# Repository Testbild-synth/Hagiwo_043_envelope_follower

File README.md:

# Hagiwo Eurorack Envelope Follower

This project is a through hole PCB version the HAGIWO 043 envelope follower. I also added a guitar jack input with more amplification to be able to plug in a variety of instruments.

## STATUS: CONFIRMED WORKING! Currently on version 2, if you ordered an older version make sure that the ground connector is correctly connected to all other pcb grounds and also check that the Guitar input is going into the C3 capacitor correctly.

## Hardware and PCB
For this one I wanted to fit it all onto one PCB and make the guitar jack fit. This was quite a task and I'm afraid the pcb ended up a bit messy in the end because of this. It still works fine, but has a lot of overlapping components and you have to be careful when building it.

You can find the schematic and BOM in the root folder. 
For the PCBs, the module has one circuit PCB and one panel PCB. 
You can order them on any common PCB manufacturing service, I used JLCPCB. For the circuit PCB, standard settings should be fine.
For the panel, since it has copper exposed, make sure to choose a lead free surface finish (LeadFree HASL, ENIG) and/or spraypaint your panels so that you don't get lead on your hands.

For assembly, the guitar jack is optional. It will stick out and has to be connected to the rest of the pcb via wires. Look for the pads named "guitar in" and "gnd" on the pcb and connect those to the inner and outer log of a mono guitar/6.5mm jack socket.
Be sure to get a pcb mount guitar jack! we will not be mounting it to the pcb but the ["normal" round ones](https://www.conrad.de/de/p/bkl-electronic-1109001-klinken-steckverbinder-6-35-mm-buchse-einbau-vertikal-polzahl-num-2-mono-silber-1-st-732931.html) don't fit the spacing. I got [this!](https://www.reichelt.de/klinkeneinbaubuchse-6-3-mm-mono-2-pol-ebmsv-63-p36198.html?PROVID=2788&gclid=CjwKCAiAsNKQBhAPEiwAB-I5zdQuMwRXD1BioeI2tvVrd7EJKaeRaZpVK8cO38NI3ps_gF-faOb4TRoCZE0QAvD_BwE)

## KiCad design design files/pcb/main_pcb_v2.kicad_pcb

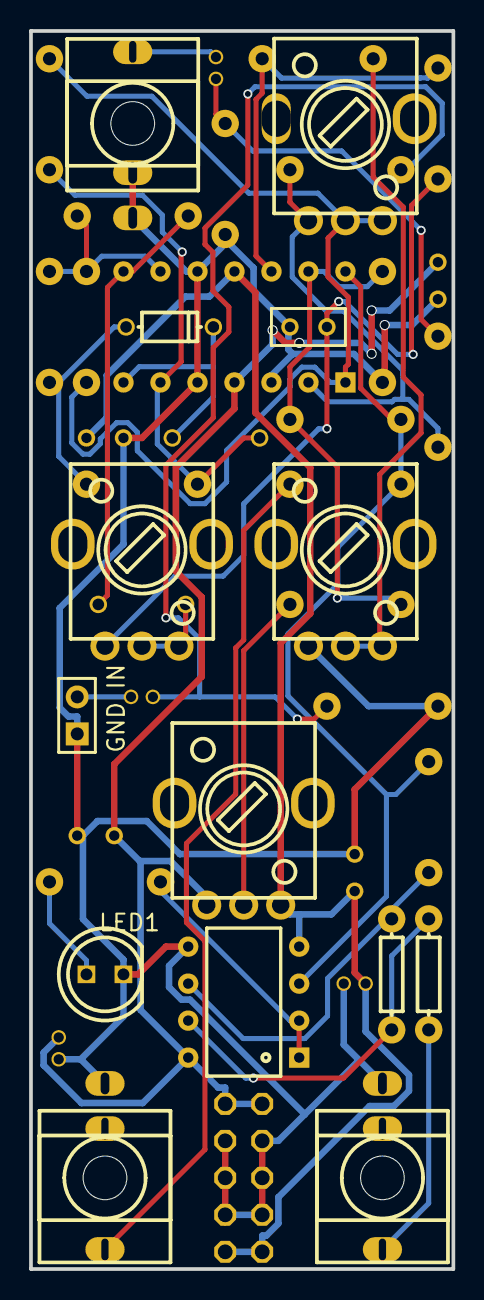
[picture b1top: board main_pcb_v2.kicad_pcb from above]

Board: 2 copper layers, 29.0 x 85.0 mm, 43 parts (0 on the bottom side), 27 nets.

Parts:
ATK: 50k; R09-5KΩ
C1, C3: 4.7u; CAP-D4.0×F1.5
C2: 1u; RAD-0.1
C4, C6, C8, C9: 100n; RAD-0.1
C5, C7: 10u; CAP-D4.0×F1.5
D1, D2, D3: DIODE1N4148; SEEED-DO-35
EP1: EURORACK_POWERHEADER_V2; EURORACK_POWER_V2
GAIN: 100k; R09-5KΩ
H1: GUITAR; HDR-F-2.54_1X2
J1: IN; THONKICONN_1
J2: OUT; THONKICONN_1
J3: INVOUT; THONKICONN_1
LED1: LED_LED5MM
OFFSET: 100k; R09-5KΩ
R1: 20k; R_AXIAL-0.3
R2: 22k; R_AXIAL-0.3
R3, R7, R8, R9, R13, R14, R15, R16, R17: 10k; R_AXIAL-0.3
R4: 47k; R_AXIAL-0.3
R5, R12, R18: 1k; R_AXIAL-0.3
R6, R11: 1M; R_AXIAL-0.3
R10, R19: 4.7k; R_AXIAL-0.3
REL: 1M; R09-5KΩ
U1: TL074CJ; DIP14
U2: TL072IPE4; DIP8

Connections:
12V: C6.2, C7.1, C8.2, EP1.12, OFFSET.1, U1.4, U2.8
-12V: C4.2, C5.2, C9.2, EP1.-12, OFFSET.3, U1.11, U2.4
C1_2: C1.2, R4.2, R6.1
C2_2: ATK.1, C2.2, R5.2
D2_C: ATK.2, ATK.3, D2.C
D3_A: D3.A, R3.1, R9.2
GND: C2.1, C4.1, C5.1, C6.1, C7.2, C8.1, C9.1, EP1.GND0, EP1.GND1, EP1.GND2, EP1.GND3, EP1.GND4, EP1.GND5, H1.1, J1.1, J1.2, J2.1, J3.1, LED1.K, R6.2, R11.2, R15.2, REL.1, U1.3, U1.5, U1.10, U2.5
H1_2: C3.1, H1.2
J1_3: C1.1, J1.3
LED: R12.1, R14.1, R17.1, U1.14, U2.3
OUT: R5.1, R7.1, U1.12
R7_2: R7.2, REL.2, REL.3
R10_2: C3.2, R10.2, R11.1
R12_2: J2.3, R12.2
R13_2: OFFSET.2, R13.2
R17_2: R16.1, R17.2, U2.6
R18_2: J3.3, R18.2
R19_2: LED1.A, R19.2
U1_1: GAIN.2, GAIN.3, R1.2, R8.2, U1.1
U1_2: GAIN.1, R4.1, R10.1, U1.2
U1_6: D1.C, R3.2, R8.1, U1.6
U1_7: D1.A, D3.C, U1.7
U1_8: D2.A, R2.1, U1.8
U1_9: R1.1, R2.2, R9.1, U1.9
U1_13: R13.1, R14.2, R15.1, U1.13
U2_1: R19.1, U2.1, U2.2
U2_7: R16.2, R18.1, U2.7

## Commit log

2022-02-01 Add files via upload
    Uploaded gerbers and design files
2022-02-22 slight changes to gerbers, now confirmed working!
2022-02-22 slight changes to pcb silkscreen
2022-02-23 upload additional images and BOM/schematic
2022-02-23 upload pcb image
2022-03-02 Version 1.2 fixes, changed Guitar jack orientation and resistor for more amplification!
2022-03-14 fixed grounding issue on pcb
